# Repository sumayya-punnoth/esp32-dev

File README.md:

# ESP32 Dev Kit

This is a custom PCB of the ESP32 development board designed in KiCad using the official Espressif documentation as reference.

## Viewing the project
1. Clone the repository:
```bash
git clone https://github.com/sumayya-punnoth/esp32-dev
```
2. Open `esp32_dev.kicad_pro` to view the schematic and PCB layout.

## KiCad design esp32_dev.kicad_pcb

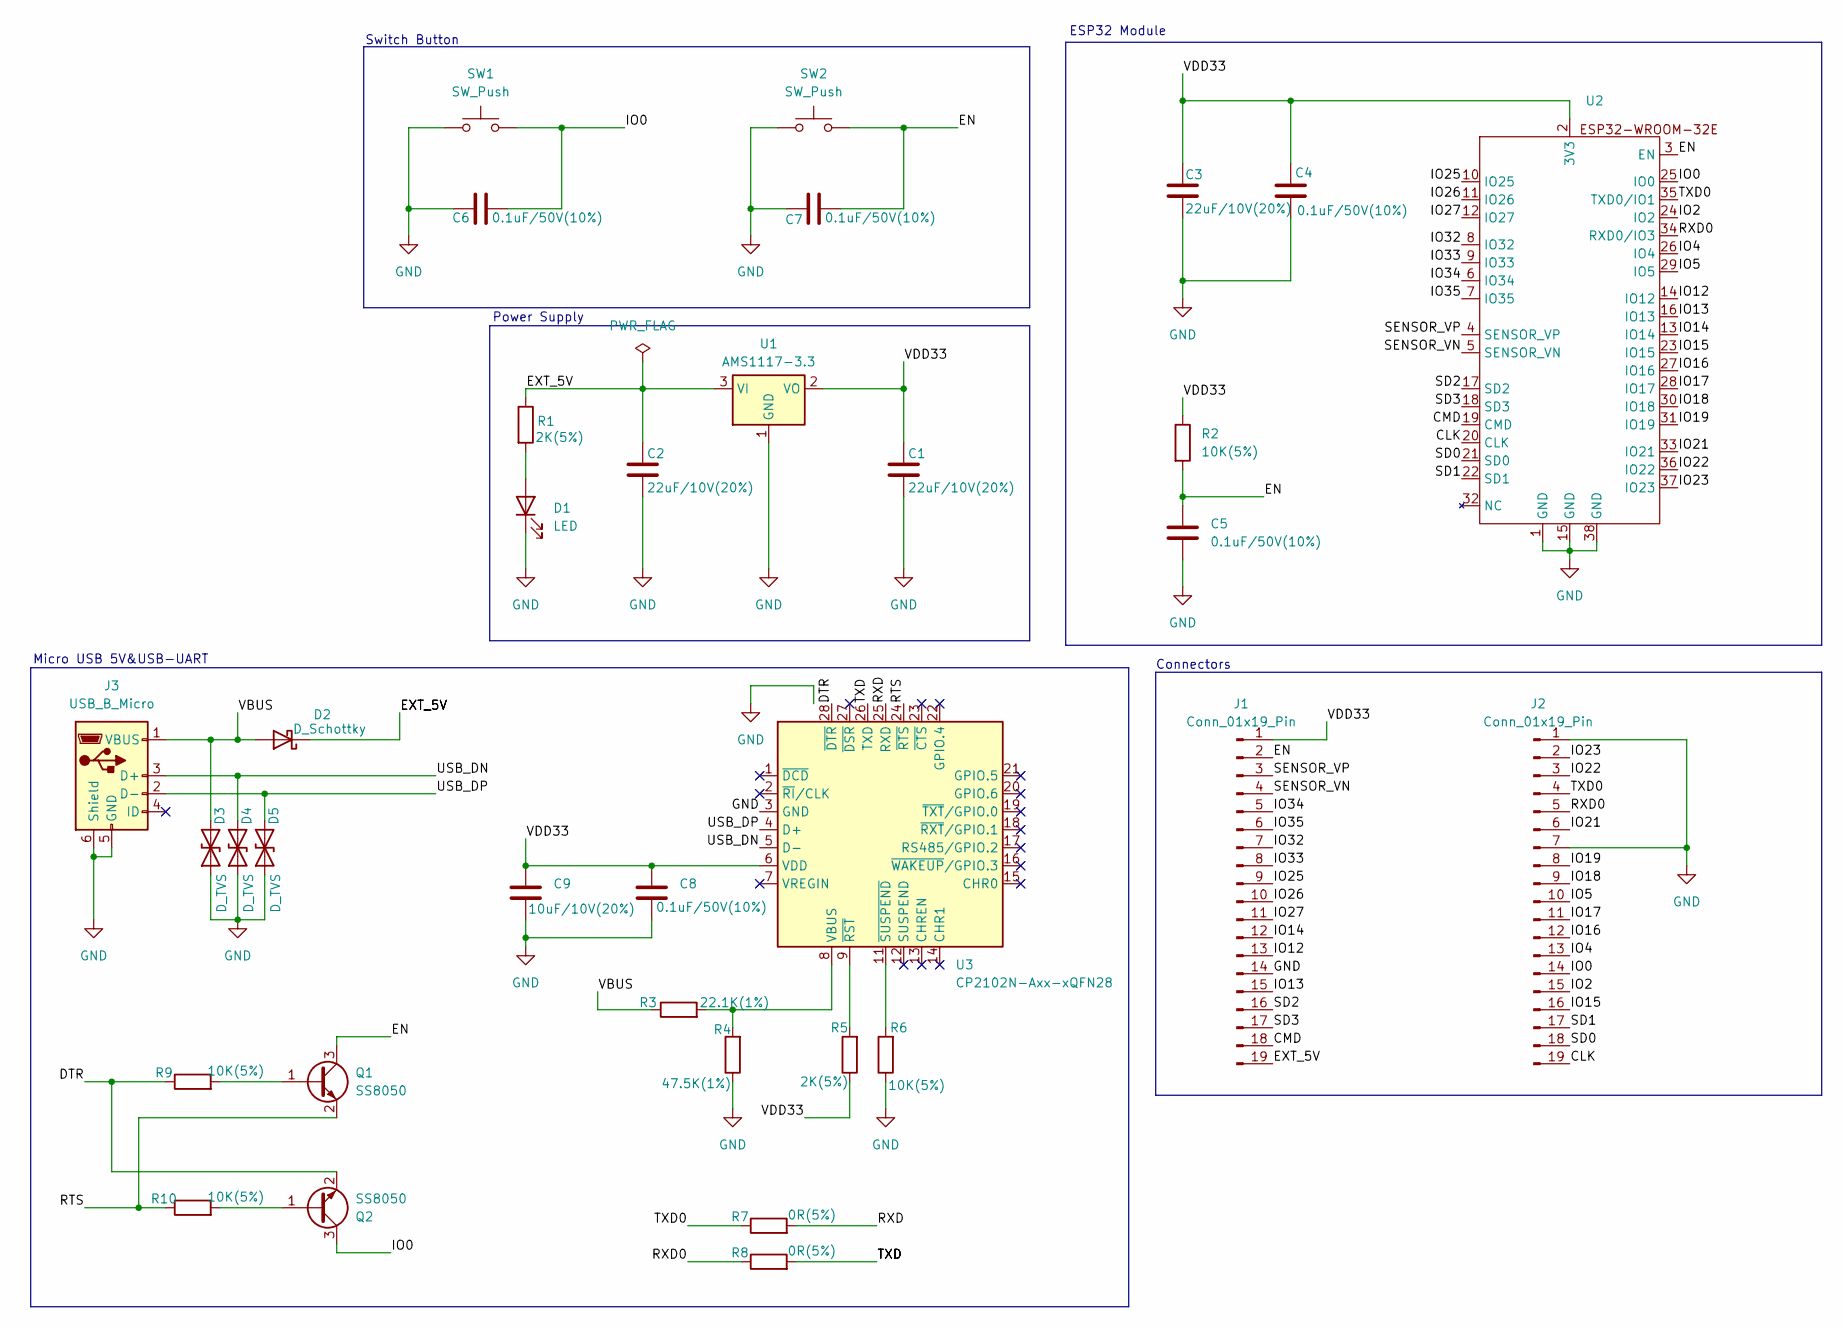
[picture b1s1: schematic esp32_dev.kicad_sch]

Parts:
C1, C2, C3: 22uF/10V(20%); C_0201_0603Metric
C4, C5, C6, C7, C8: 0.1uF/50V(10%); C_01005_0402Metric
C9: 10uF/10V(20%); C_01005_0402Metric
D1: LED; LED_0603_1608Metric
D2: D_Schottky; D_SOD-323
D3, D4, D5: D_TVS; D_SOD-523
J1, J2: Conn_01x19_Pin; PinHeader_1x19_P2.54mm_Vertical
J3: USB_B_Micro; USB_Micro-AB_Molex_47590-0001
Q1, Q2: SS8050; SOT-23
R1, R5: 2K(5%); R_01005_0402Metric
R2, R6, R9, R10: 10K(5%); R_01005_0402Metric
R3: 22.1K(1%); R_01005_0402Metric
R4: 47.5K(1%); R_01005_0402Metric
R7, R8: 0R(5%); R_01005_0402Metric
SW1, SW2: SW_Push; SW_SPST_B3S-1000
U1: AMS1117-3.3; SOT-223-3_TabPin2
U2: Untitled
U3: CP2102N-Axx-xQFN28; QFN-28-1EP_5x5mm_P0.5mm_EP3.35x3.35mm

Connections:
/CLK: J2.19, U2.20 (CLK)
/CMD: J1.18, U2.19 (CMD)
/DTR: Q2.2 (E), R9.1, U3.28 (~DTR)
/EN: C5.1, C7.1, J1.2, Q1.3 (C), R2.2, SW2.2, U2.3 (EN); also elsewhere on the board
/EXT_5V: C2.1, D2.1 (K), J1.19, R1.1, U1.3 (VI)
/IO0: C6.1, J2.14, Q2.3 (C), SW1.2, U2.25 (IO0); also elsewhere on the board
/IO2: J2.15, U2.24 (IO2)
/IO4: J2.13, U2.26 (IO4)
/IO5: J2.10, U2.29 (IO5)
/IO12: J1.13, U2.14 (IO12)
/IO13: J1.15, U2.16 (IO13)
/IO14: J1.12, U2.13 (IO14)
/IO15: J2.16, U2.23 (IO15)
/IO16: J2.12, U2.27 (IO16)
/IO17: J2.11, U2.28 (IO17)
/IO18: J2.9, U2.30 (IO18)
/IO19: J2.8, U2.31 (IO19)
/IO21: J2.6, U2.33 (IO21)
/IO22: J2.3, U2.36 (IO22)
/IO23: J2.2, U2.37 (IO23)
/IO25: J1.9, U2.10 (IO25)
/IO26: J1.10, U2.11 (IO26)
/IO27: J1.11, U2.12 (IO27)
/IO32: J1.7, U2.8 (IO32)
/IO33: J1.8, U2.9 (IO33)
/IO34: J1.5, U2.6 (IO34)
/IO35: J1.6, U2.7 (IO35)
/RTS: Q1.2 (E), R10.1, U3.24 (~RTS)
/RXD: R7.2, U3.25 (RXD)
/RXD0: J2.5, R8.1, U2.34 (RXD0/IO3)
/SD0: J2.18, U2.21 (SD0)
/SD1: J2.17, U2.22 (SD1)
/SD2: J1.16, U2.17 (SD2)
/SD3: J1.17, U2.18 (SD3)
/SENSOR_VN: J1.4, U2.5 (SENSOR_VN)
/SENSOR_VP: J1.3, U2.4 (SENSOR_VP)
/TXD: R8.2, U3.26 (TXD)
/TXD0: J2.4, R7.1, U2.35 (TXD0/IO1)
/USB_DN: D4.2 (A2), J3.3 (D+), U3.5 (D-)
/USB_DP: D5.2 (A2), J3.2 (D-), U3.4 (D+)
/VBUS: D2.2 (A), D3.2 (A2), J3.1 (VBUS), R3.1
/VDD33: C1.1, C3.1, C4.1, C8.1, C9.1, J1.1, R2.1, R5.1, U1.2 (VO), U2.2 (3V3), U3.6 (VDD)
GND: C1.2, C2.2, C3.2, C4.2, C5.2, C6.2, C7.2, C8.2, C9.2, D1.1 (K), D3.1 (A1), D4.1 (A1), D5.1 (A1), J1.14, J2.1, J2.7, J3.5 (GND), J3.6 (Shield), R4.1, R6.1, SW1.1, SW2.1, U1.1 (GND), U2.1 (GND), U2.15 (GND), U2.38 (GND), U3.3 (GND), U3.29 (GND); also elsewhere on the board
unnamed: D1.2 (A), R1.2
unnamed: Q1.1 (B), R9.2
unnamed: Q2.1 (B), R10.2
unnamed: R3.2, R4.2, U3.8 (VBUS)
unnamed: R5.2, U3.9 (~RST)
unnamed: R6.2, U3.11 (~SUSPEND)

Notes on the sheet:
Switch Button
Connectors
Power Supply
ESP32 Module
Micro USB 5V&USB-UART

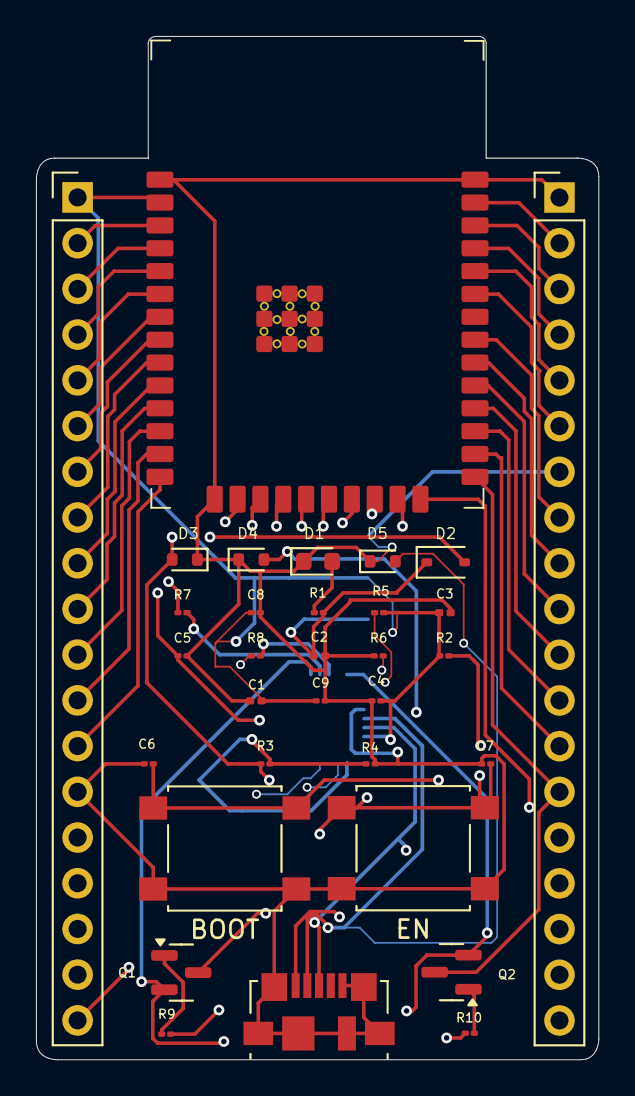
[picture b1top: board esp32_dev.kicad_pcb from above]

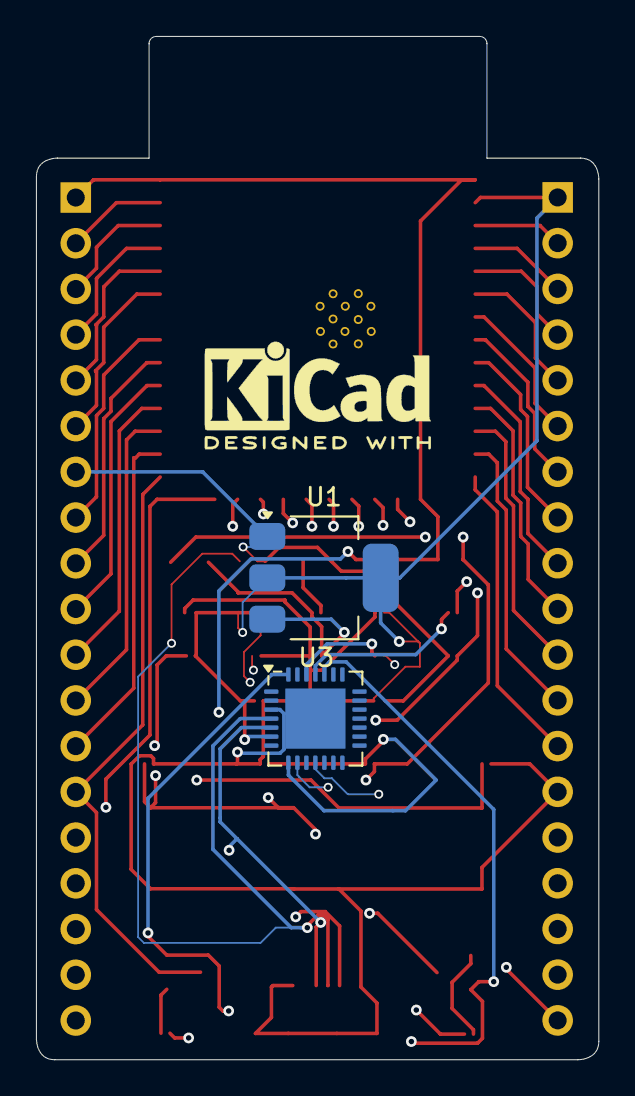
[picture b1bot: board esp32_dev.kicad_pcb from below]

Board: 4 copper layers, 31.2 x 56.8 mm, 34 parts (2 on the bottom side), 49 nets.

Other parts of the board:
BOOT: SW_Push; SW_SPST_B3S-1000
EN: SW_Push; SW_SPST_B3S-1000

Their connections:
/EN: EN.2; also elsewhere on the board
/IO0: BOOT.2; also elsewhere on the board
GND: BOOT.1, EN.1; also elsewhere on the board

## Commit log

2025-08-11 pcb modified
